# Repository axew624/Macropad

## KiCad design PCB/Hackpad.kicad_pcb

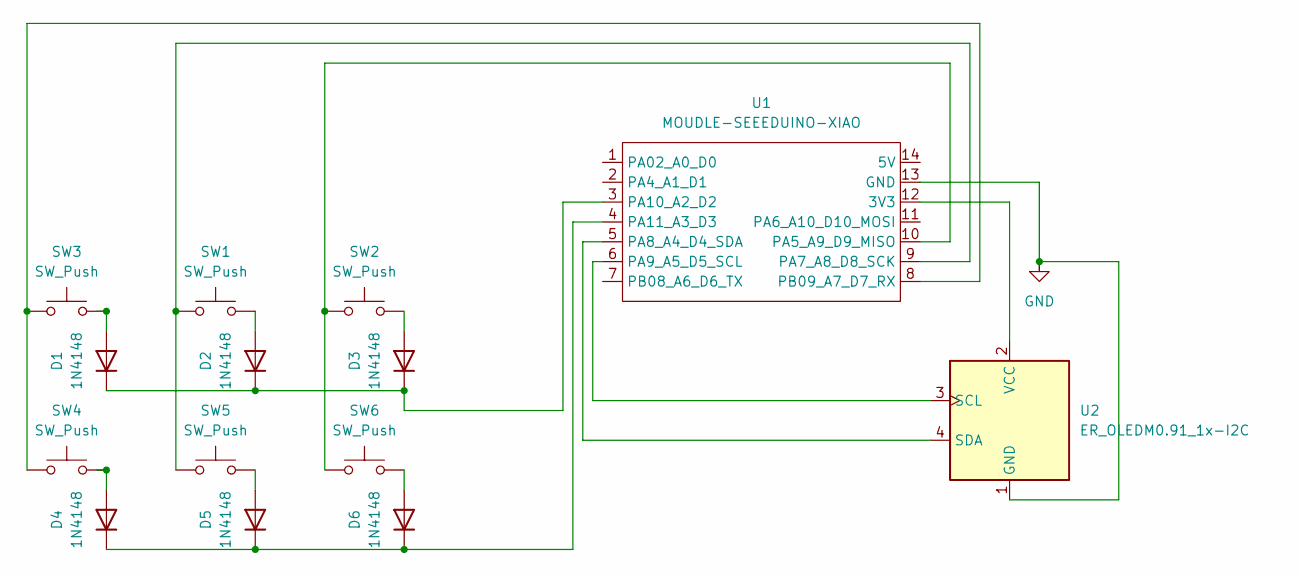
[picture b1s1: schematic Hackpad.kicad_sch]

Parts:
D1, D2, D3, D4, D5, D6: 1N4148; D_DO-35_SOD27_P7.62mm_Horizontal
SW1, SW2, SW3, SW4, SW5, SW6: SW_Push; SW_Cherry_MX_1.00u_PCB
U1: MOUDLE-SEEEDUINO-XIAO; XIAO-Generic-Hybrid-14P-2.54-21X17.8MM
U2: ER_OLEDM0.91_1x-I2C; SSD1306-0.91-OLED-4pin-128x32

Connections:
GND: U1.13 (GND), U2.1 (GND)
unnamed: D1.2 (A), SW3.2
unnamed: D1.1 (K), D2.1 (K), D3.1 (K), U1.3 (PA10_A2_D2)
unnamed: D2.2 (A), SW1.2
unnamed: D3.2 (A), SW2.2
unnamed: D4.2 (A), SW4.2
unnamed: D4.1 (K), D5.1 (K), D6.1 (K), U1.4 (PA11_A3_D3)
unnamed: D5.2 (A), SW5.2
unnamed: D6.2 (A), SW6.2
unnamed: U1.12 (3V3), U2.2 (VCC)
unnamed: SW2.1, SW6.1, U1.10 (PA5_A9_D9_MISO)
unnamed: SW1.1, SW5.1, U1.9 (PA7_A8_D8_SCK)
unnamed: U1.5 (PA8_A4_D4_SDA), U2.4 (SDA)
unnamed: U1.6 (PA9_A5_D5_SCL), U2.3 (SCL)
unnamed: SW3.1, SW4.1, U1.8 (PB09_A7_D7_RX)

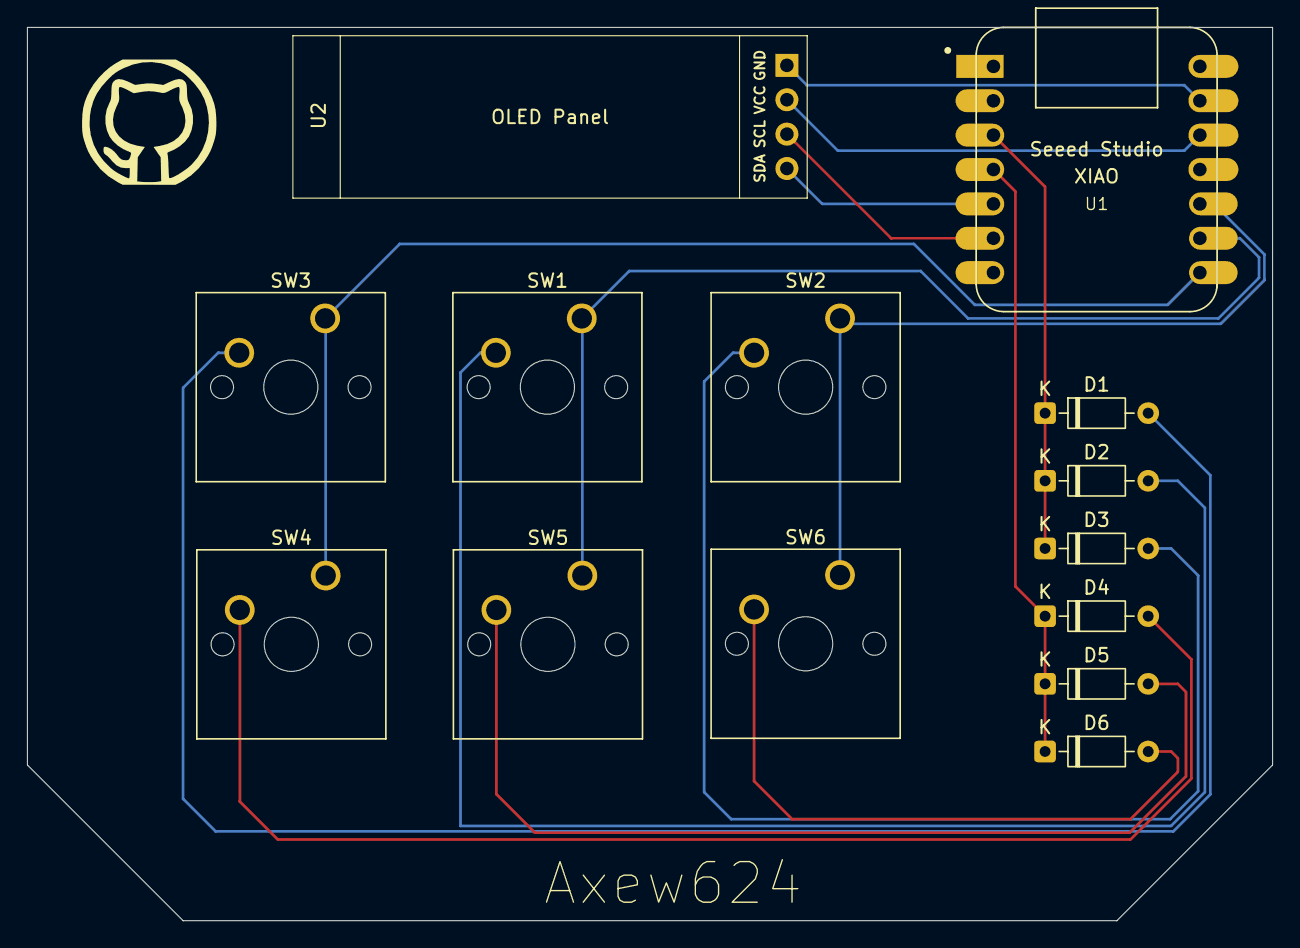
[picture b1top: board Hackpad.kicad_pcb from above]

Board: 2 copper layers, 92.0 x 66.0 mm, 14 parts (0 on the bottom side), 15 nets.
